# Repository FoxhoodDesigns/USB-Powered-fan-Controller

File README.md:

# USB-Powered-fan Controller
This small device is designed to allow one to power and control a 12V (case)fan from a standard 5V 1A USB charger.
Intended application are small DIY fan projects such as a Desktop fan using a Noctua NV-AA1-12, Fume Extracters and Part cooling.
## Overal design:
The controller can be divided into four parts:
- A 5V->12V Boost converter based on a LMR62421XMF reference design
- A Load switch using a PMV50PEAR and a BSS138.
- A ATTiny414 that is handling PWM generation and I/O
- The I/O itself consisting of (charlieplexed) leds, Encoder, USB-C port and two 4-pin FAN pinouts
## Working
On power-up the controller will try to spin up the fan to about half speed via a 25Khz PWM signal, measure the RPM, set PWM to 80% and check if there was significant change.
If there was, then it assumes the FAN is PWM compatible and keep to using PWM, if not it will assume the FAN is DC and instead starts pulsing the Load Switch.

During operation one can set the speed of the fan anywhere between 40 and 100 percent. Pressing the encoder SW causes the controller to halt the fan till pressed again

If during operation the FAN either halts OR speeds up too much (wip), the controller will immediately shut off power and remain locked till it got power-cycled as a protection measure against sudden jamming/defects.

### TODO:
- Gerber upload
- Overhaul the code and implement a speed up detection test.
- Test with other fans.
- BOM upload
- Potentially setting up for manufacturing by PCBWay/JLCPCB
- Verify if possible to program via AVRDUDE using CH340

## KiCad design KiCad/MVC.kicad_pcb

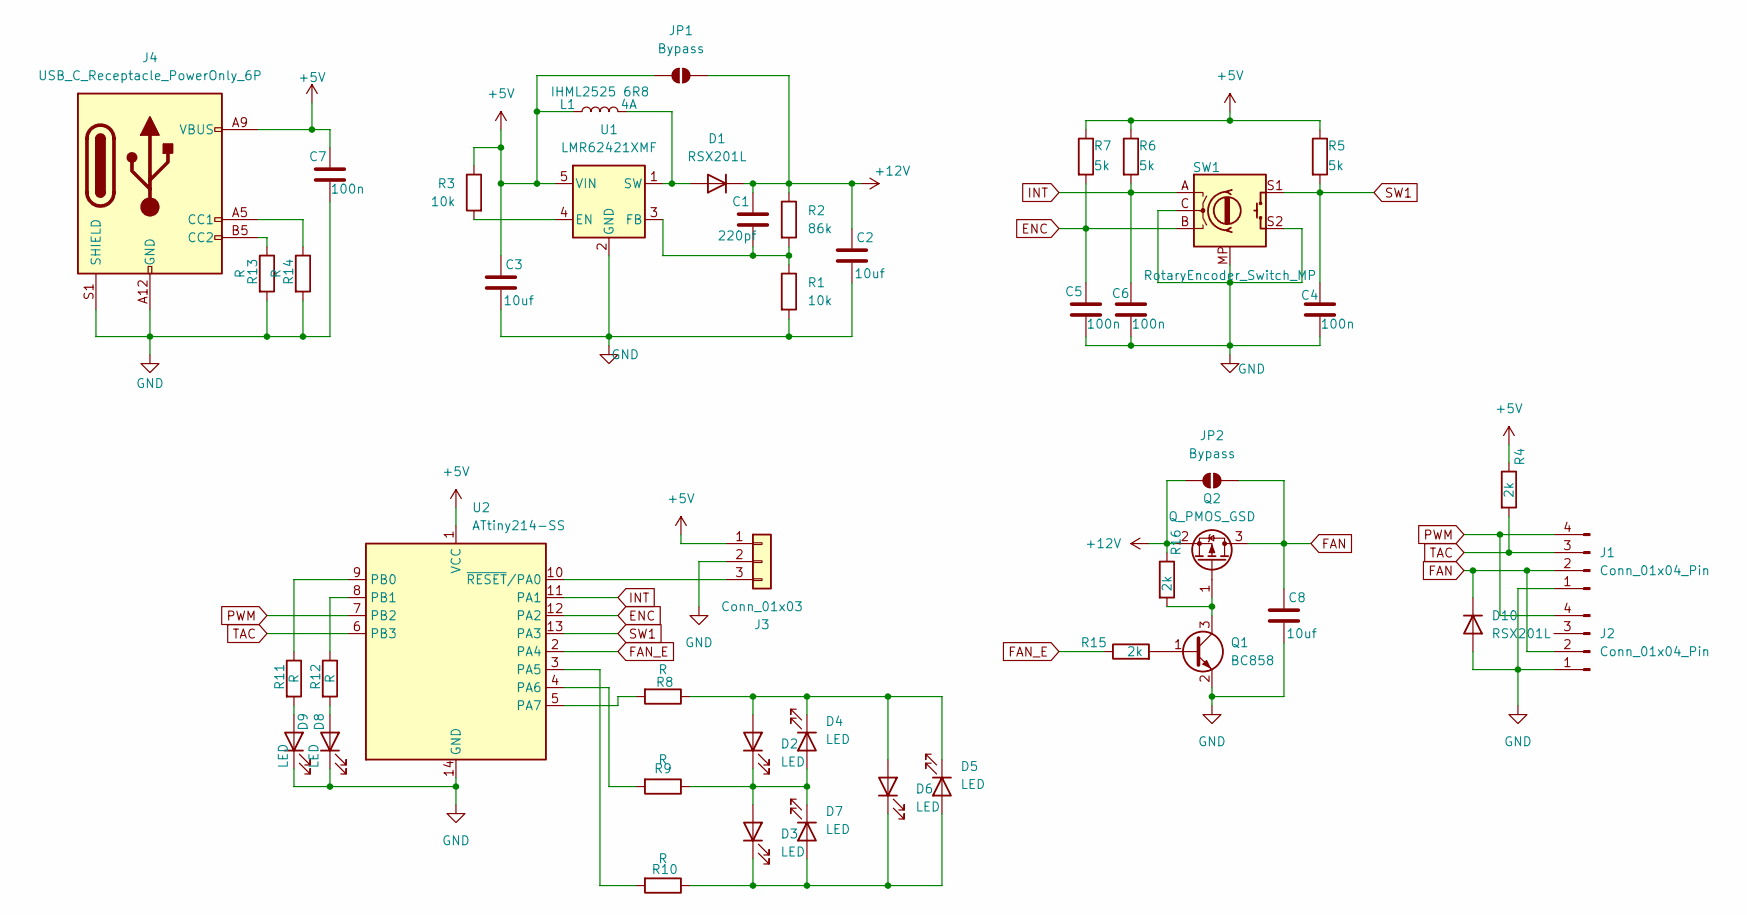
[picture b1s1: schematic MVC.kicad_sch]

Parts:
C1: 220pf; C_0805_2012Metric_Pad1.18x1.45mm_HandSolder; Voltage 1kV; Tolerance 100%
C2, C3, C8: 10uf; C_1210_3225Metric_Pad1.33x2.70mm_HandSolder; Voltage 1kV; Tolerance 100%
C4, C5, C6, C7: 100n; C_0805_2012Metric_Pad1.18x1.45mm_HandSolder; Voltage 1kV; Tolerance 100%
D1, D10: RSX201L; D_SMA_Handsoldering
D2, D3, D4, D5, D6, D7, D8, D9: LED; LED_0805_2012Metric_Pad1.15x1.40mm_HandSolder
J1, J2: Conn_01x04_Pin; FanPinHeader_1x04_P2.54mm_Vertical
J3: Conn_01x03; PinHeader_1x03_P2.54mm_Vertical
J4: USB_C_Receptacle_PowerOnly_6P; USB_C_Receptacle_GCT_USB4125-xx-x_6P_TopMnt_Horizontal
JP1, JP2: Bypass; SolderJumper-2_P1.3mm_Open_Pad1.0x1.5mm
L1: IHML2525 6R8; L_Vishay_IHLP-2525
Q1: BC858; SOT-23
Q2: Q_PMOS_GSD; SOT-23
R1, R3: 10k; R_0805_2012Metric_Pad1.20x1.40mm_HandSolder
R2: 86k; R_0805_2012Metric_Pad1.20x1.40mm_HandSolder
R4, R15, R16: 2k; R_0805_2012Metric_Pad1.20x1.40mm_HandSolder
R5, R6, R7: 5k; R_0805_2012Metric_Pad1.20x1.40mm_HandSolder
R8, R9, R10, R11, R12, R13, R14: R; R_0805_2012Metric_Pad1.20x1.40mm_HandSolder
SW1: RotaryEncoder_Switch_MP; RotaryEncoder_Bourns_Vertical_PEC12R-3x17F-Sxxxx
U1: LMR62421XMF; SOT-23-5
U2: ATtiny214-SS; SOIC-14_3.9x8.7mm_P1.27mm

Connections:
+5V: C3.1, C7.1, J3.1, J4.A9 (VBUS), J4.B9 (VBUS), JP1.1 (A), L1.1, R3.1, R4.1, R5.1, R6.1, R7.1, U1.5 (VIN), U2.1 (VCC)
+12V: C1.1, C2.1, D1.1 (K), JP1.2 (B), JP2.1 (A), Q2.2 (S), R2.1, R16.1
ENC: C5.1, R7.2, SW1.B, U2.12 (PA2)
FAN: C8.1, D10.1 (K), J1.2, J2.2, JP2.2 (B), Q2.3 (D)
FAN_E: R15.1, U2.2 (PA4)
GND: C2.2, C3.2, C4.2, C5.2, C6.2, C7.2, C8.2, D8.1 (K), D9.1 (K), D10.2 (A), J1.1, J2.1, J3.2, J4.A12 (GND), J4.B12 (GND), J4.S1 (SHIELD), Q1.2 (E), R1.2, R13.2, R14.2, SW1.C, SW1.MP, SW1.S2, U1.2 (GND), U2.14 (GND)
INT: C6.1, R6.2, SW1.A, U2.11 (PA1)
unnamed: D1.2 (A), L1.2, U1.1 (SW)
unnamed: D2.2 (A), D4.1 (K), D5.1 (K), D6.2 (A), R8.1
unnamed: D2.1 (K), D3.2 (A), D4.2 (A), D7.1 (K), R9.1
unnamed: D3.1 (K), D5.2 (A), D6.1 (K), D7.2 (A), R10.1
unnamed: D8.2 (A), R12.2
unnamed: D9.2 (A), R11.2
unnamed: J3.3, U2.10 (~RESET/PA0)
unnamed: J4.A5 (CC1), R14.1
unnamed: J4.B5 (CC2), R13.1
unnamed: Q1.1 (B), R15.2
unnamed: Q1.3 (C), Q2.1 (G), R16.2
unnamed: R3.2, U1.4 (EN)
unnamed: C1.2, R1.1, R2.2, U1.3 (FB)
unnamed: R10.2, U2.3 (PA5)
unnamed: R9.2, U2.4 (PA6)
unnamed: R8.2, U2.5 (PA7)
unnamed: R11.1, U2.9 (PB0)
unnamed: R12.1, U2.8 (PB1)
PWM: J1.4, J2.4, U2.7 (PB2)
SW1: C4.1, R5.2, SW1.S1, U2.13 (PA3)
TAC: J1.3, R4.2, U2.6 (PB3)

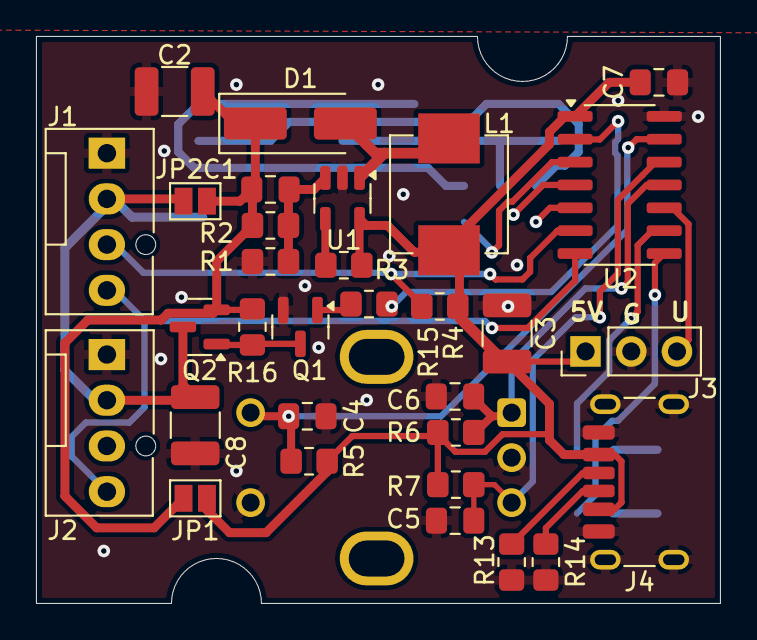
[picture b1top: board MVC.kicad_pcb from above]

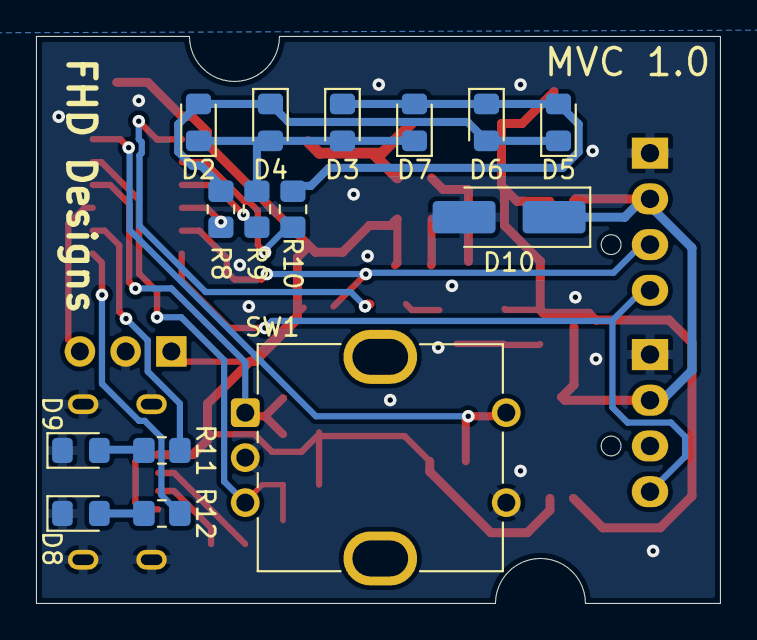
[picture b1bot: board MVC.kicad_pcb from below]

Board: 2 copper layers, 38.0 x 31.5 mm, 46 parts (15 on the bottom side), 28 nets.

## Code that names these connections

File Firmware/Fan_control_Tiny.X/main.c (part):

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//Pin bitmasks
#define G_LED 0x01
#define R_LED 0x02
#define TAC 0x08
#define ENC 0x04
#define ENC_SW 0x08
#define FAN_E 0x10
#define PWM 0x04
//Macros
#define ERROR 0
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
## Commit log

2024-10-14 Initial upload
    Initial upload of KiCAD and MPLAB files.
2024-10-14 Update README.md
    Quick readme update
